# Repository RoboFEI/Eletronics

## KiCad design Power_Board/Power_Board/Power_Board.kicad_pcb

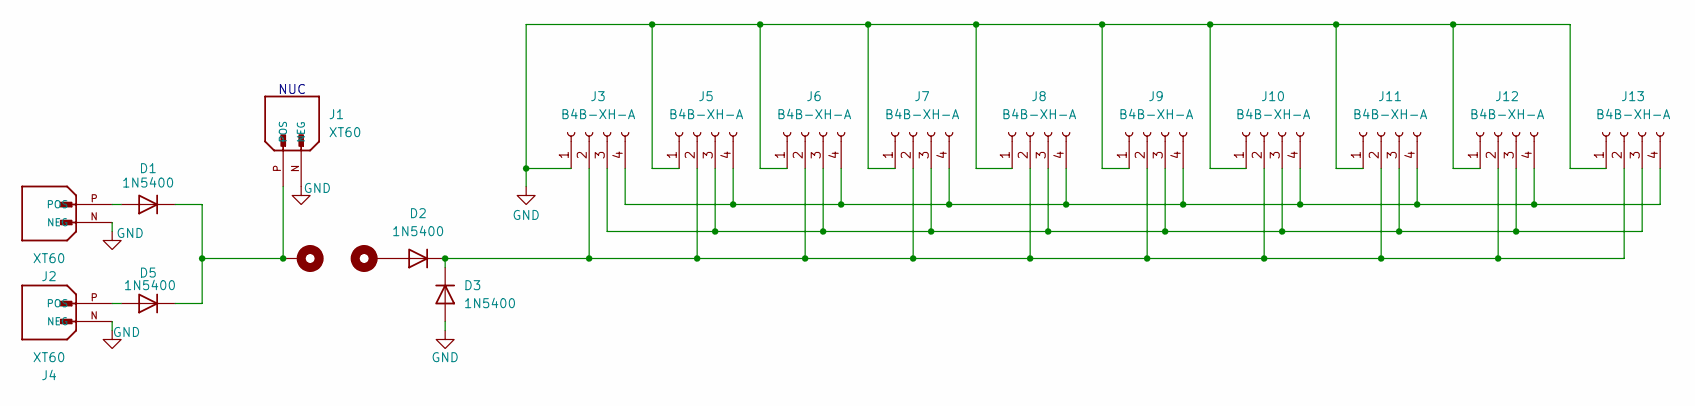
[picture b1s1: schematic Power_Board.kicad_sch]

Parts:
D1, D2, D3, D5: 1N5400; D_DO-201AD_P15.24mm_Horizontal
H1, H3: MountingHole_Pad; MountingHole_2.5mm_Pad
J1, J2, J4: XT60; XT60-M_Vertical; PARTREV V1.2
J3, J5, J6, J7, J8, J9, J10, J11, J12, J13: B4B-XH-A; XM_conn_vertical-B4B-EH-A; PARTREV 7/4/21

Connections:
GND: D3.2 (A), J1.N (NEG), J2.N (NEG), J3.1 (GND), J4.N (NEG), J5.1 (GND), J6.1 (GND), J7.1 (GND), J8.1 (GND), J9.1 (GND), J10.1 (GND), J11.1 (GND), J12.1 (GND), J13.1 (GND)
unnamed: D1.2 (A), J2.P (POS)
unnamed: D1.1 (K), D5.1 (K), H3.1, J1.P (POS)
unnamed: D2.2 (A), H1.1
unnamed: D2.1 (K), D3.1 (K), J3.2 (VDD), J5.2 (VDD), J6.2 (VDD), J7.2 (VDD), J8.2 (VDD), J9.2 (VDD), J10.2 (VDD), J11.2 (VDD), J12.2 (VDD), J13.2 (VDD)
unnamed: D5.2 (A), J4.P (POS)
unnamed: J3.3 (D+), J5.3 (D+), J6.3 (D+), J7.3 (D+), J8.3 (D+), J9.3 (D+), J10.3 (D+), J11.3 (D+), J12.3 (D+), J13.3 (D+)
unnamed: J3.4 (D-), J5.4 (D-), J6.4 (D-), J7.4 (D-), J8.4 (D-), J9.4 (D-), J10.4 (D-), J11.4 (D-), J12.4 (D-), J13.4 (D-)

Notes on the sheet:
NUC

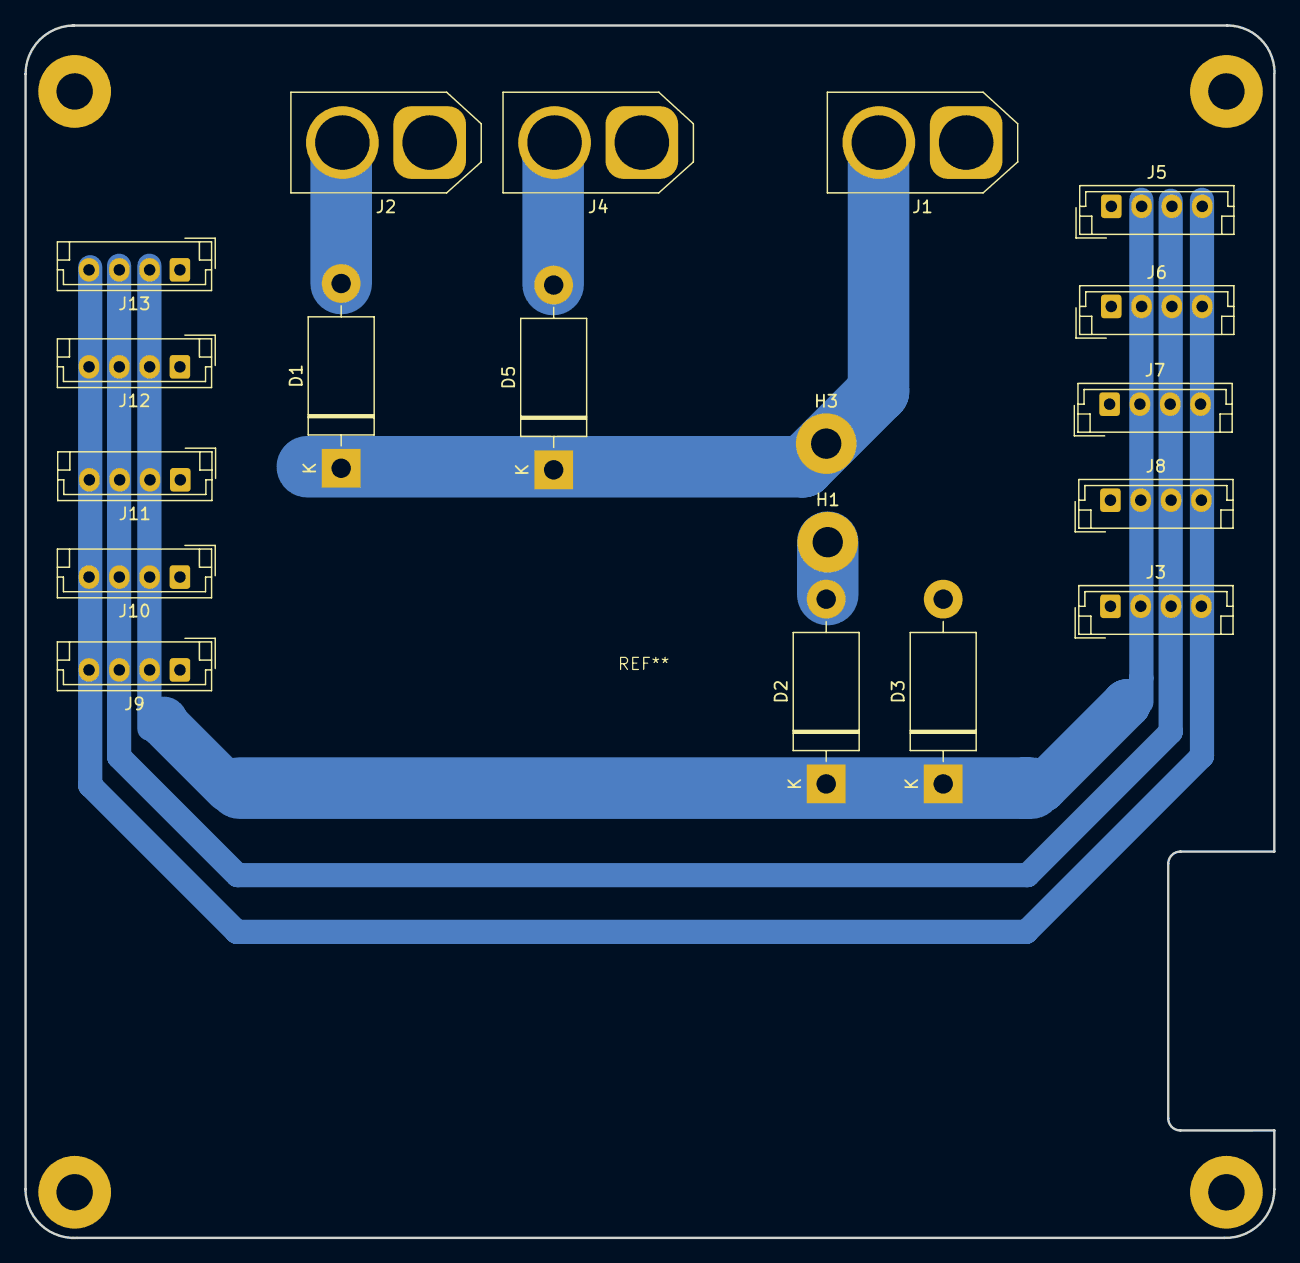
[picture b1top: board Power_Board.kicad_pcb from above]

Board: 2 copper layers, 103.0 x 100.0 mm, 19 parts (0 on the bottom side), 8 nets.

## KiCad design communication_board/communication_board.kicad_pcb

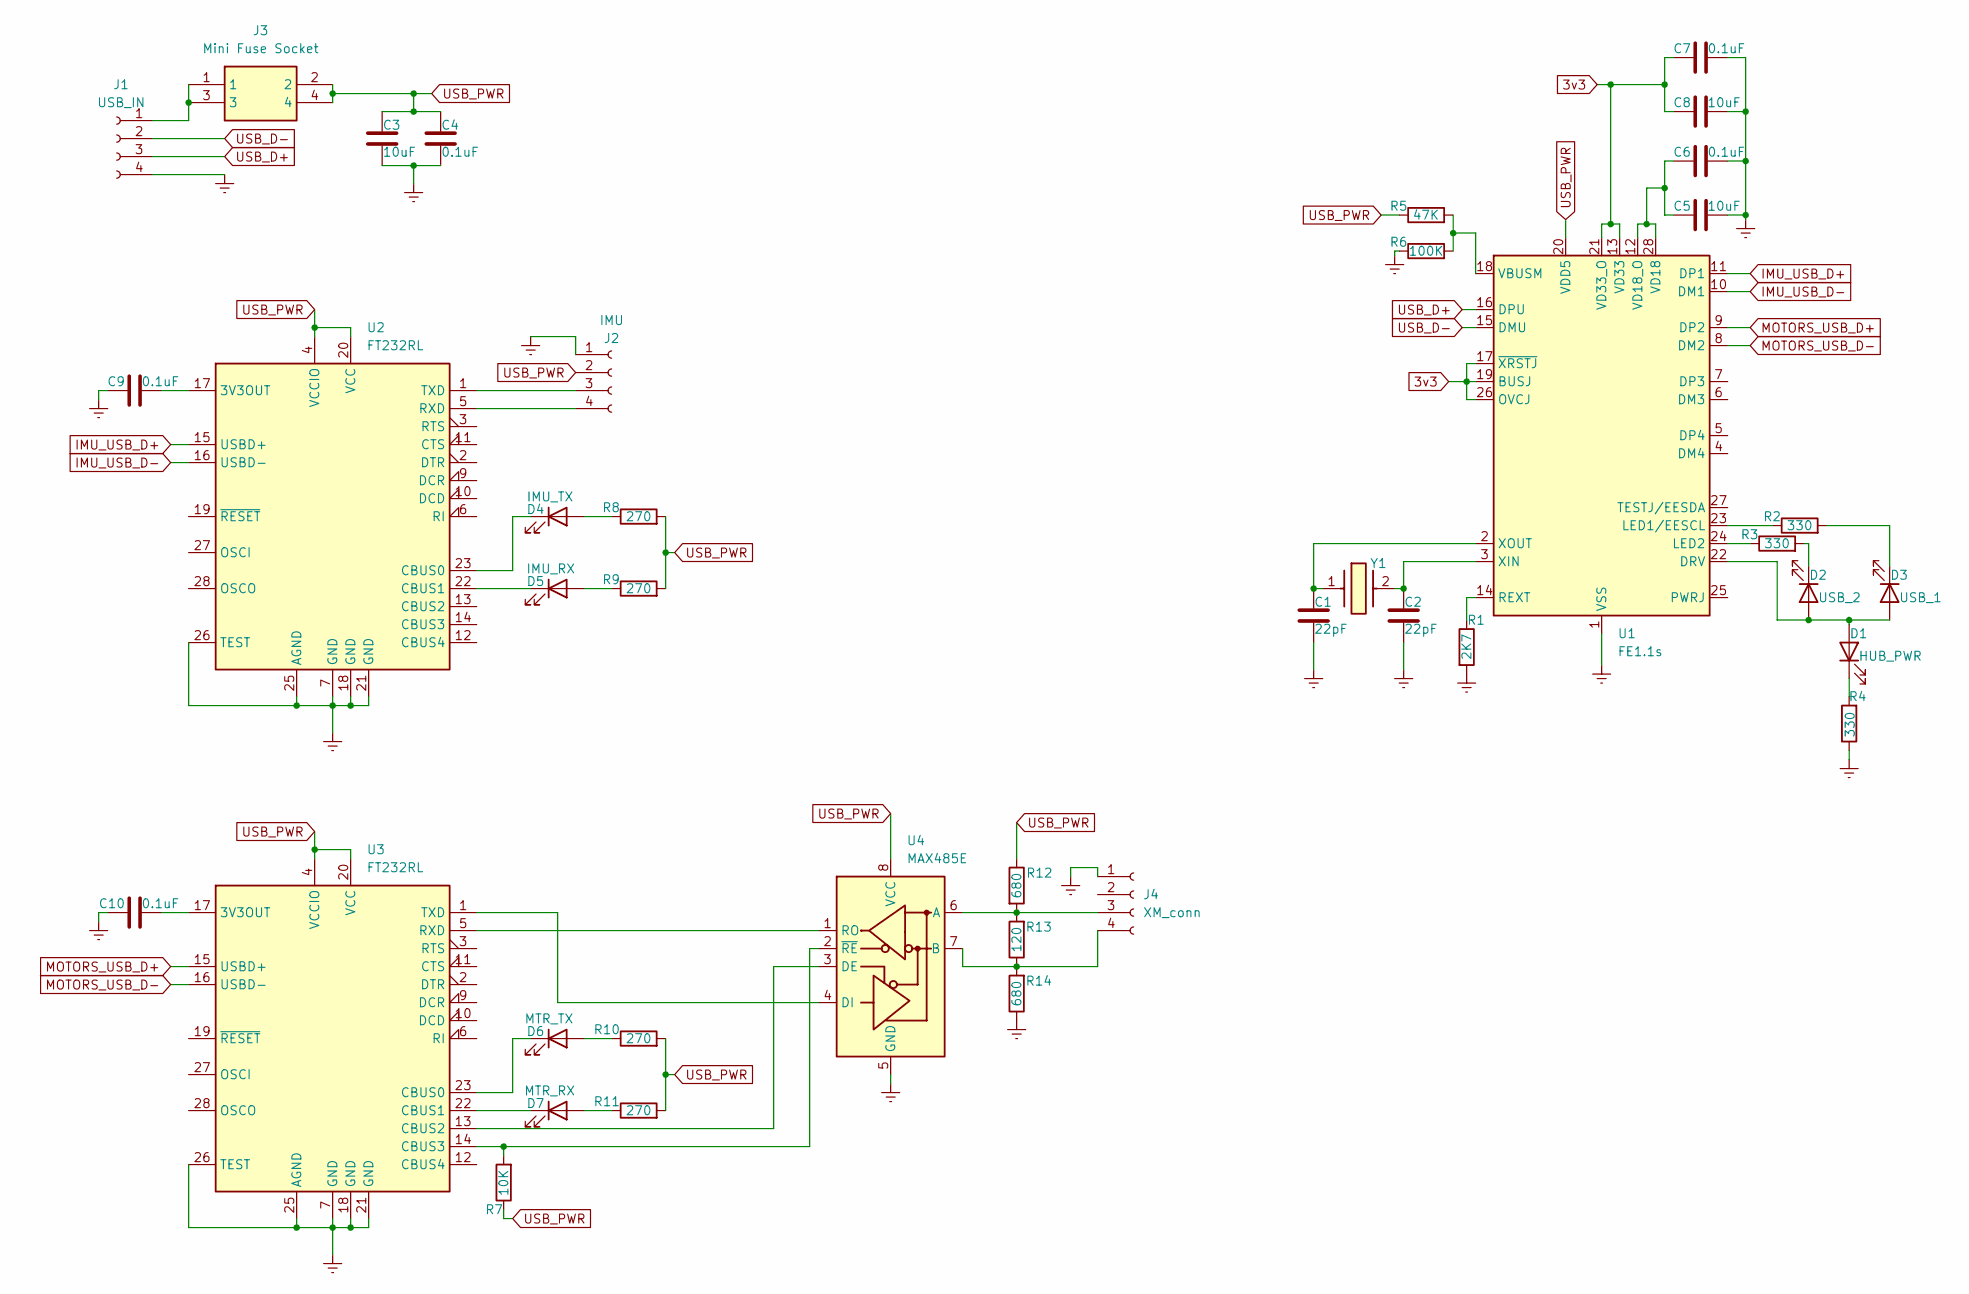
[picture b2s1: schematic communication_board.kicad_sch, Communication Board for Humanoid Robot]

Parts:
C1, C2: 22pF; C_1206_3216Metric
C3, C5, C8: 10uF; C_1206_3216Metric
C4, C6, C7, C9, C10: 0.1uF; C_1206_3216Metric
D1: HUB_PWR; LED_1206_3216Metric_Pad1.42x1.75mm_HandSolder
D2: USB_2; LED_1206_3216Metric_Pad1.42x1.75mm_HandSolder
D3: USB_1; LED_1206_3216Metric_Pad1.42x1.75mm_HandSolder
D4: IMU_TX; LED_1206_3216Metric_Pad1.42x1.75mm_HandSolder
D5: IMU_RX; LED_1206_3216Metric_Pad1.42x1.75mm_HandSolder
D6: MTR_TX; LED_1206_3216Metric_Pad1.42x1.75mm_HandSolder
D7: MTR_RX; LED_1206_3216Metric_Pad1.42x1.75mm_HandSolder
J1: USB_IN; PinHeader_1x04_P2.54mm_Vertical
J2: IMU; PinHeader_1x04_P2.54mm_Vertical
J3: Mini Fuse Socket; Mouser Part Number 534-3557-2
J4: XM_conn; XM_conn_vertical-B4B-EH-A
R1: 2K7; R_1206_3216Metric
R2, R3, R4: 330; R_1206_3216Metric
R5: 47K; R_1206_3216Metric
R6: 100K; R_1206_3216Metric
R7: 10K; R_1206_3216Metric
R8, R9, R10, R11: 270; R_1206_3216Metric
R12, R14: 680; R_1206_3216Metric
R13: 120; R_1206_3216Metric
U1: FE1.1s; SSOP-28_3.9x9.9mm_P0.635mm
U2, U3: FT232RL; SSOP-28_5.3x10.2mm_P0.65mm
U4: MAX485E; SOIC-8_3.9x4.9mm_P1.27mm
Y1: Crystal 12MHz - ECS; Mouser Part Number 520-120-18-5PX-GM-TR

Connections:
3v3: C7.1, C8.1, U1.13 (VD33), U1.17 (~XRSTJ), U1.19 (BUSJ), U1.21 (VD33_O), U1.26 (OVCJ)
GNDREF: C1.2, C2.2, C3.2, C4.2, C5.2, C6.2, C7.2, C8.2, C9.1, C10.1, J1.4, J2.1, J4.1 (GND), R1.2, R4.1, R6.1, R14.1, U1.1 (VSS), U2.7 (GND), U2.18 (GND), U2.21 (GND), U2.25 (AGND), U2.26 (TEST), U3.7 (GND), U3.18 (GND), U3.21 (GND), U3.25 (AGND), U3.26 (TEST), U4.5 (GND)
IMU_USB_D+: U1.11 (DP1), U2.15 (USBD+)
IMU_USB_D-: U1.10 (DM1), U2.16 (USBD-)
MOTORS_USB_D+: U1.9 (DP2), U3.15 (USBD+)
MOTORS_USB_D-: U1.8 (DM2), U3.16 (USBD-)
unnamed: D1.2 (A), D2.2 (A), D3.2 (A), U1.22 (DRV)
unnamed: D1.1 (K), R4.2
unnamed: D2.1 (K), R3.2
unnamed: D3.1 (K), R2.2
unnamed: D4.2 (A), R8.1
unnamed: D4.1 (K), U2.23 (CBUS0)
unnamed: D5.2 (A), R9.1
unnamed: D5.1 (K), U2.22 (CBUS1)
unnamed: D6.2 (A), R10.1
unnamed: D6.1 (K), U3.23 (CBUS0)
unnamed: D7.2 (A), R11.1
unnamed: D7.1 (K), U3.22 (CBUS1)
unnamed: J1.1, J3.1, J3.3
unnamed: J2.3, U2.1 (TXD)
unnamed: J2.4, U2.5 (RXD)
unnamed: J4.3 (D+), R12.2, R13.2, U4.6 (A)
unnamed: J4.4 (D-), R13.1, R14.2, U4.7 (B)
unnamed: R2.1, U1.23 (LED1/EESCL)
unnamed: R3.1, U1.24 (LED2)
unnamed: R1.1, U1.14 (REXT)
unnamed: R5.2, R6.2, U1.18 (VBUSM)
unnamed: C5.1, C6.1, U1.12 (VD18_O), U1.28 (VD18)
unnamed: C2.1, U1.3 (XIN), Y1.2
unnamed: C1.1, U1.2 (XOUT), Y1.1
unnamed: C9.2, U2.17 (3V3OUT)
unnamed: C10.2, U3.17 (3V3OUT)
unnamed: U3.13 (CBUS2), U4.3 (DE)
unnamed: R7.2, U3.14 (CBUS3), U4.2 (~RE)
unnamed: U3.5 (RXD), U4.1 (RO)
unnamed: U3.1 (TXD), U4.4 (DI)
USB_D+: J1.3, U1.16 (DPU)
USB_D-: J1.2, U1.15 (DMU)
USB_PWR: C3.1, C4.1, J2.2, J3.2, J3.4, R5.1, R7.1, R8.2, R9.2, R10.2, R11.2, R12.1, U1.20 (VDD5), U2.4 (VCCIO), U2.20 (VCC), U3.4 (VCCIO), U3.20 (VCC), U4.8 (VCC)

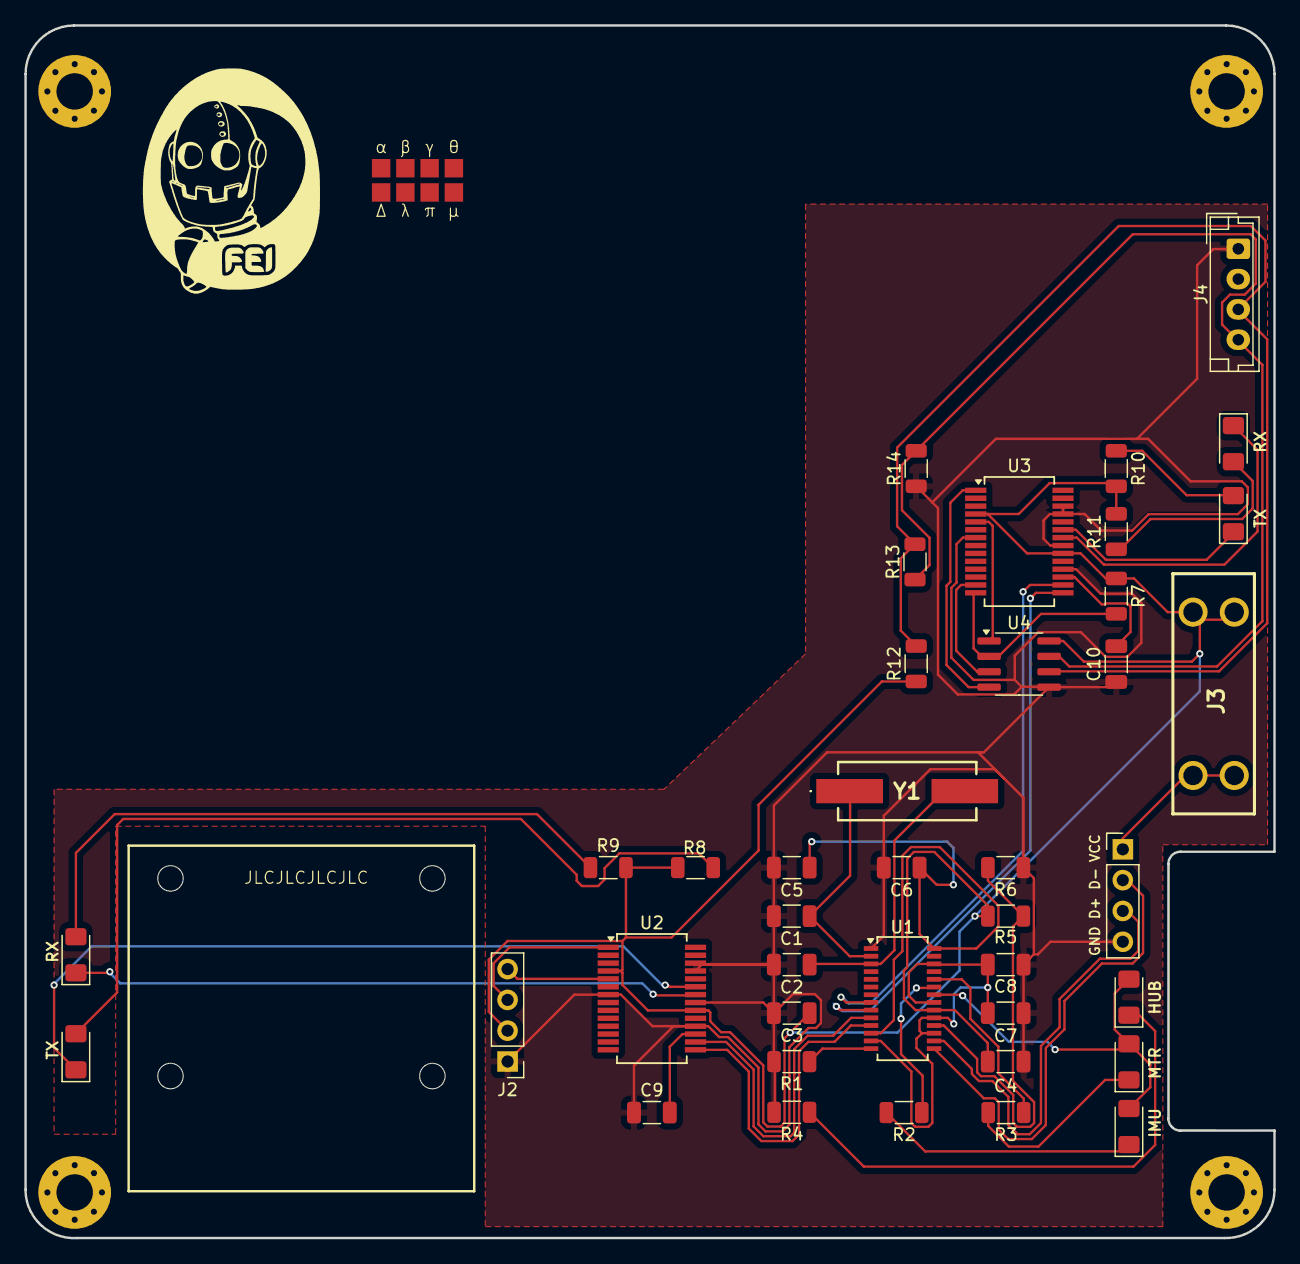
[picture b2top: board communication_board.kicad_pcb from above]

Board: 2 copper layers, 103.0 x 100.0 mm, 40 parts (0 on the bottom side), 39 nets.

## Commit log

2024-09-18 Communication board v1.0
2024-09-18 Organizing Comm board folder
2024-09-18 add setup file and git ignore
2024-09-19 add bom list
2024-09-28 update Libraries and Power Board
2024-10-29 Add inicio de placa de potencia para testes
2024-11-05 Update setup.sh for more be more practice and rename comm_board for Communication_Board
